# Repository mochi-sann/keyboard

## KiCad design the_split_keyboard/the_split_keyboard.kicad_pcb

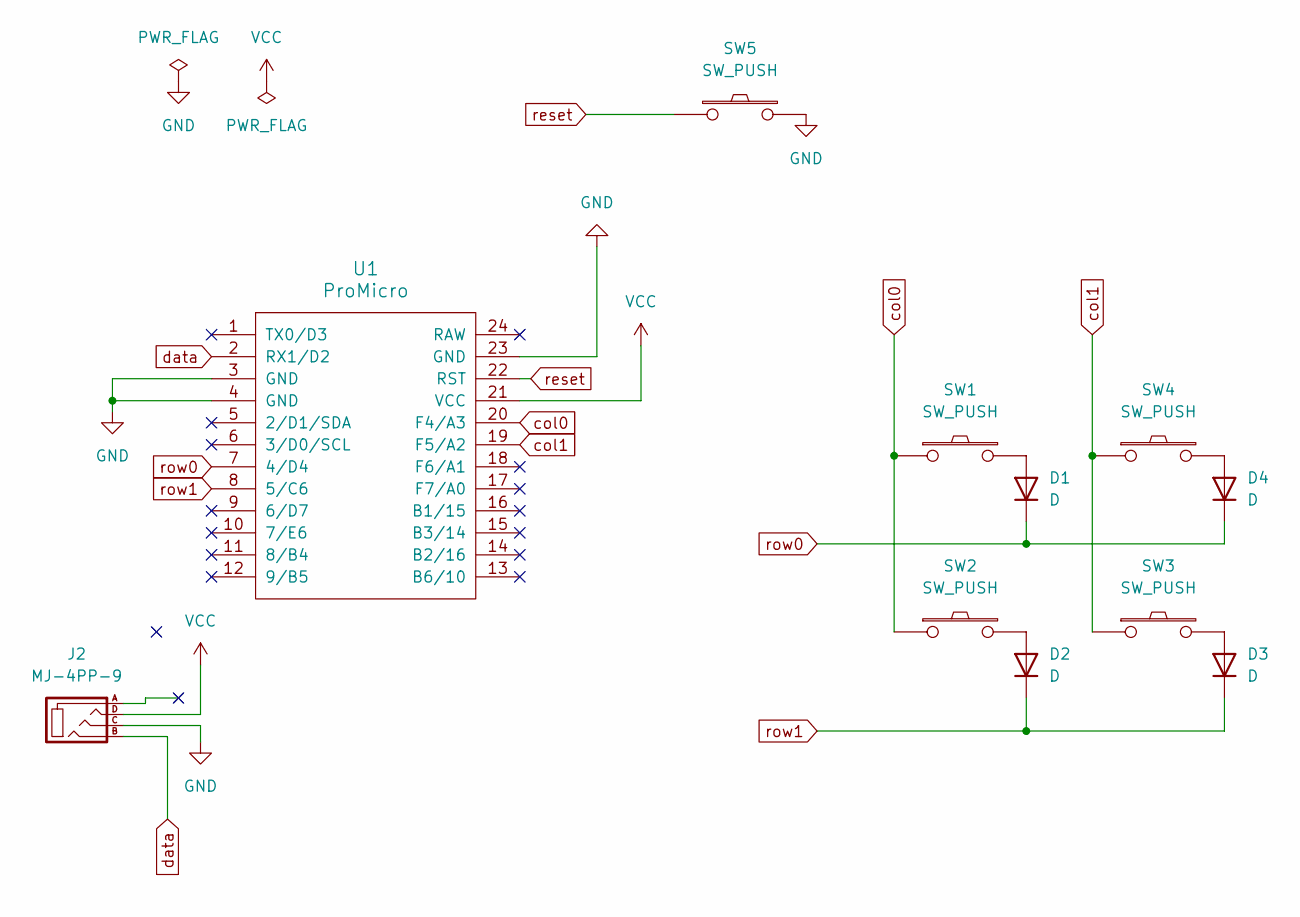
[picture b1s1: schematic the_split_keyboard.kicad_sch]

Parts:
D1, D2, D3, D4: D; D3_TH_SMD
J2: MJ-4PP-9
SW1, SW2, SW3, SW4: SW_PUSH; MX_Choc_Hotswap
SW5: SW_PUSH; ResetSW
U1: ProMicro; ProMicro_v2

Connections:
GND: J2.C, SW5.2, U1.3 (GND), U1.4 (GND), U1.23 (GND)
unnamed: D1.2 (A), SW1.2
unnamed: D2.2 (A), SW2.2
unnamed: D3.2 (A), SW3.2
unnamed: D4.2 (A), SW4.2
VCC: J2.D, U1.21 (VCC)
col0: SW1.1, SW2.1, U1.20 (F4/A3)
col1: SW3.1, SW4.1, U1.19 (F5/A2)
data: J2.B, U1.2 (RX1/D2)
reset: SW5.1, U1.22 (RST)
row0: D1.1 (K), D4.1 (K), U1.7 (4/D4)
row1: D2.1 (K), D3.1 (K), U1.8 (5/C6)

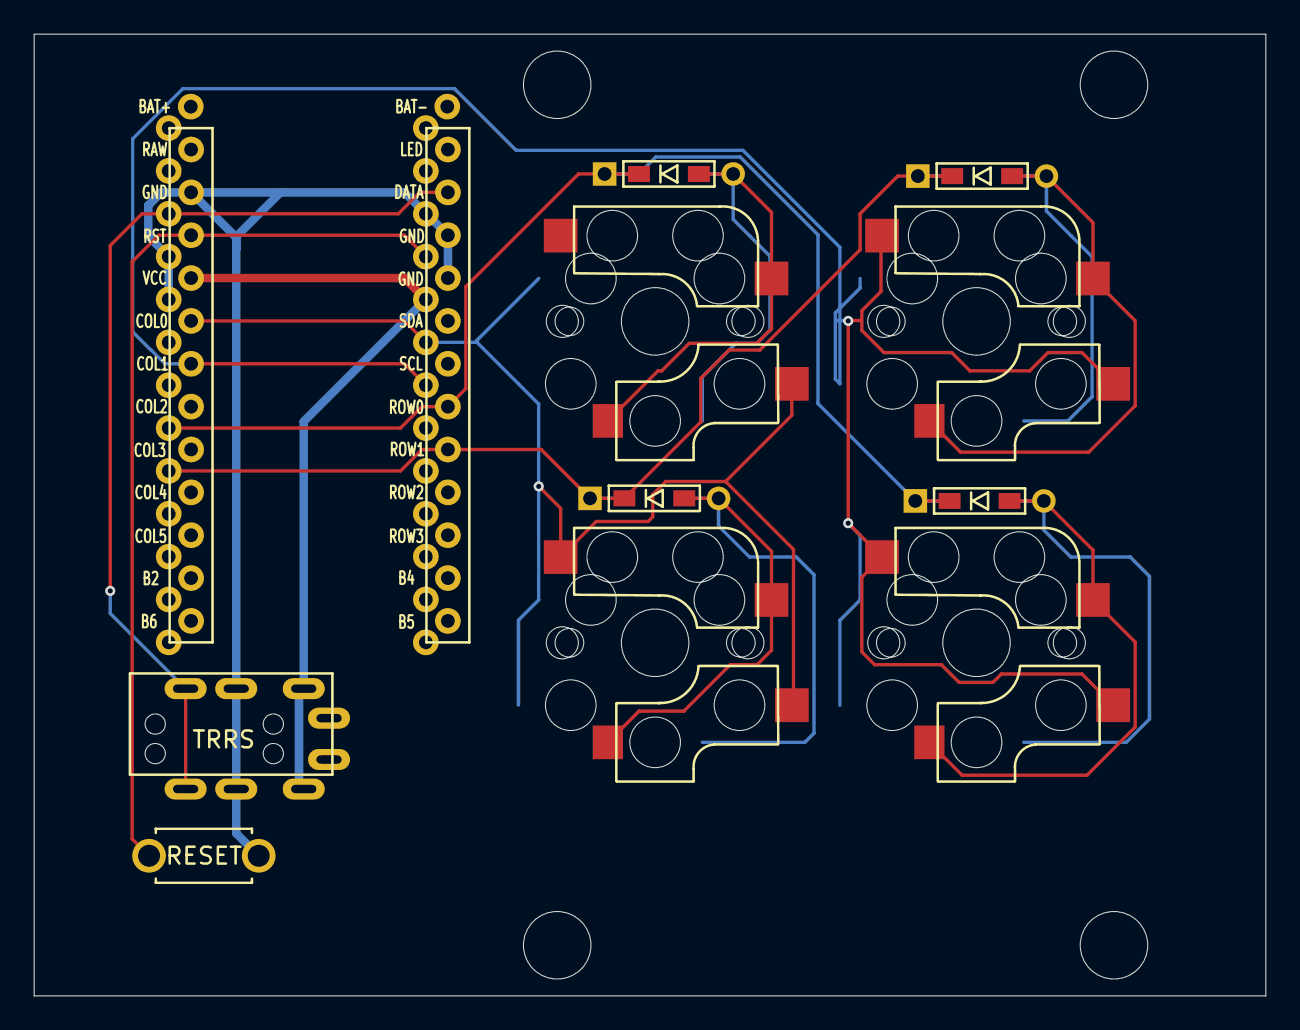
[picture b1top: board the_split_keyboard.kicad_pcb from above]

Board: 2 copper layers, 73.0 x 57.0 mm, 11 parts (0 on the bottom side), 12 nets.

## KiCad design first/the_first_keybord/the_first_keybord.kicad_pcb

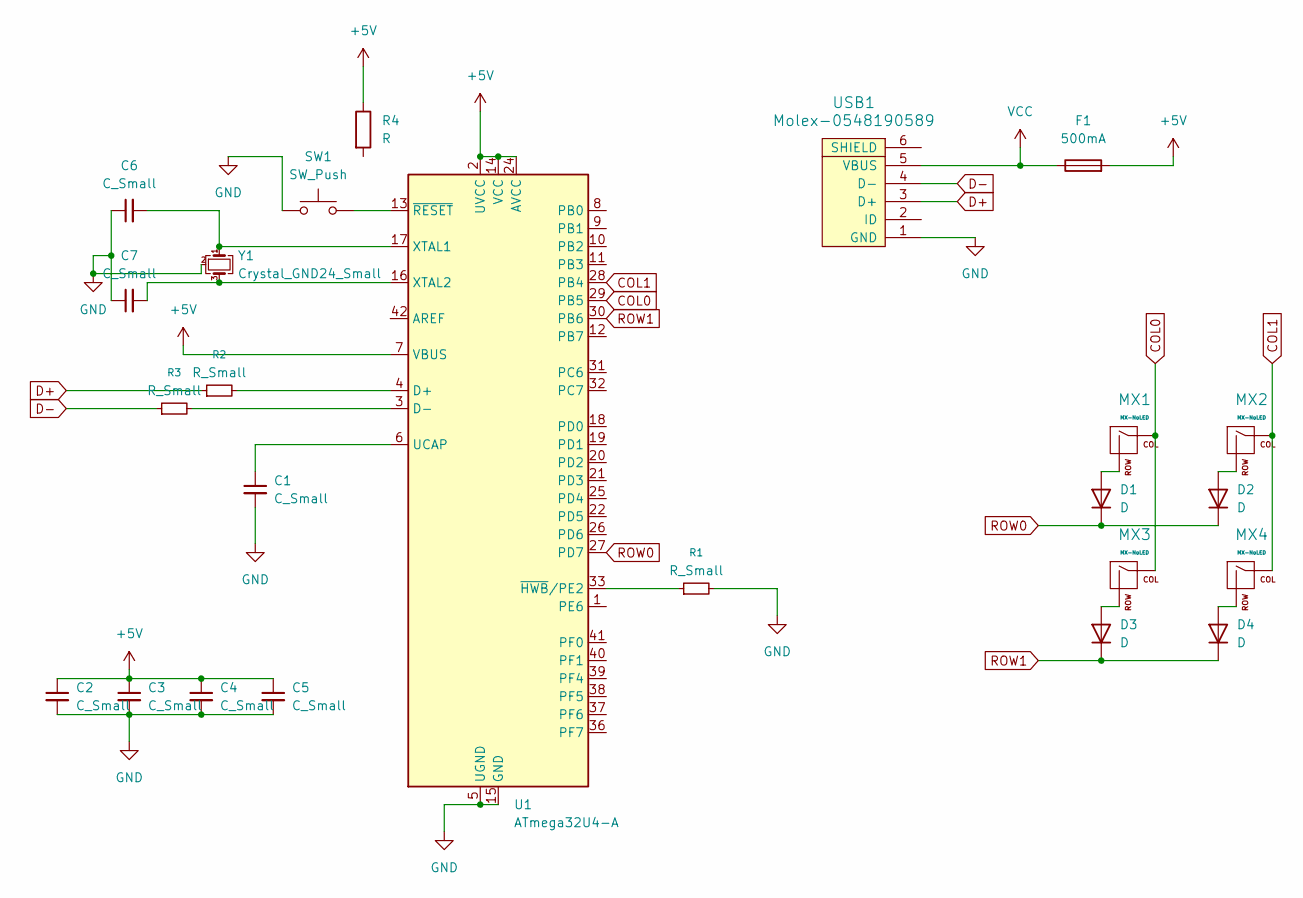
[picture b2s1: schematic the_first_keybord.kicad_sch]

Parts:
C1, C2, C3, C4, C5, C6, C7: C_Small; C_0805_2012Metric
D1, D2, D3, D4: D; D_SOD-123
F1: 500mA; Fuse_1206_3216Metric
MX1, MX2, MX3, MX4: MX-NoLED; MXOnly-1U-Hotswap-Antishear
R1, R2, R3: R_Small; R_0805_2012Metric
R4: R; R_0805_2012Metric
SW1: SW_Push; SKQG-1155865
U1: ATmega32U4-A; TQFP-44_10x10mm_P0.8mm
USB1: Molex-0548190589
Y1: Crystal_GND24_Small; Crystal_SMD_3225-4Pin_3.2x2.5mm

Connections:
+5V: C2.1, C3.1, C4.1, C5.1, F1.2, R4.1, U1.2 (UVCC), U1.7 (VBUS), U1.14 (VCC), U1.24 (AVCC), U1.34 (VCC), U1.44 (AVCC)
COL0: MX1.1 (COL), MX3.1 (COL), U1.29 (PB5)
COL1: MX2.1 (COL), MX4.1 (COL), U1.28 (PB4)
D+: R2.1, USB1.3 (D+)
D-: R3.1, USB1.4 (D-)
GND: C1.2, C2.2, C3.2, C4.2, C5.2, C6.1, C7.1, R1.2, SW1.1, U1.5 (UGND), U1.15 (GND), U1.23 (GND), U1.35 (GND), U1.43 (GND), USB1.1 (GND), Y1.2 (G), Y1.4 (G)
unnamed: D1.2 (A), MX1.2 (ROW)
unnamed: D2.2 (A), MX2.2 (ROW)
unnamed: D3.2 (A), MX3.2 (ROW)
unnamed: D4.2 (A), MX4.2 (ROW)
unnamed: R2.2, U1.4 (D+)
unnamed: R3.2, U1.3 (D-)
unnamed: C1.1, U1.6 (UCAP)
unnamed: C6.2, U1.17 (XTAL1), Y1.1
unnamed: C7.2, U1.16 (XTAL2), Y1.3
unnamed: R1.1, U1.33 (~HWB/PE2)
unnamed: SW1.2, U1.13 (~RESET)
ROW0: D1.1 (K), D2.1 (K), U1.27 (PD7)
ROW1: D3.1 (K), D4.1 (K), U1.30 (PB6)
VCC: F1.1, USB1.5 (VBUS)

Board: 2 copper layers, 24 parts (0 on the bottom side), 20 nets, no tracks yet.

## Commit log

2026-05-06 init
2026-05-06 add submodule
2026-05-06 add lib
2026-05-06 色々更新
2026-05-06 フットプリントを割り当て
2026-05-10 add keyboard
2026-05-10 ライブラリを追加
2026-05-10 色々追加
